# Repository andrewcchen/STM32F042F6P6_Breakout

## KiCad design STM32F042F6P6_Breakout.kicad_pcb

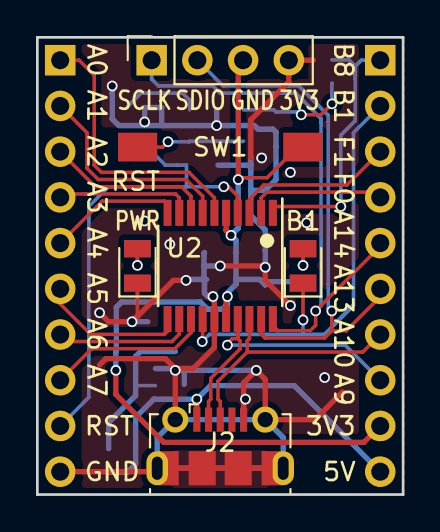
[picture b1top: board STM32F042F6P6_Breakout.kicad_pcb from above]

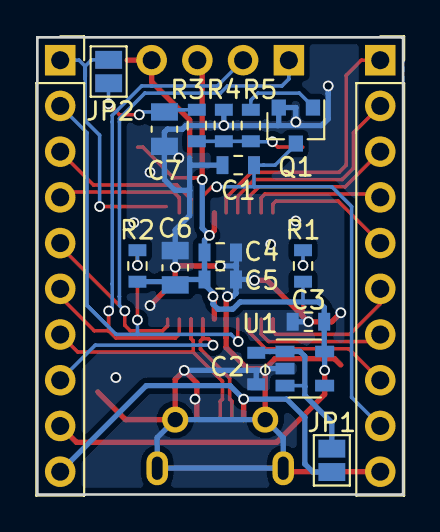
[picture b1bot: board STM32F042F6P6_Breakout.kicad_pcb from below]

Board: 2 copper layers, 20.3 x 25.4 mm, 24 parts (18 on the bottom side), 26 nets.

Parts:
C1, C4, C5: 100nF; C_0603_1608Metric
C2, C3: 1uF; C_0603_1608Metric
C6, C7: 10uF; C_0805_2012Metric
D1, D2: LED; LED_0805_2012Metric
J1, J3: Conn_01x10_Male; PinSocket_1x10_P2.54mm_Vertical
J2: USB_B_Micro; USB_Micro-B_Molex-105017-0001
J4: Conn_01x04_Male; PinSocket_1x04_P2.54mm_Vertical
JP1, JP2: SolderJumper; SolderJumper-2_P1.3mm_Open_Pad1.0x1.5mm
Q1: Q_NPN; SOT-23
R1, R2: 470; R_0603_1608Metric
R3: 330k; R_0603_1608Metric
R4, R5: 10k; R_0603_1608Metric
SW1: SW_Push; SW_SPST_FSMSM
U1: TLV70033_SOT23-5; SOT-23-5
U2: STM32F042F6Px; TSSOP-20_4.4x6.5mm_P0.65mm

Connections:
+3V3: C3.1, C4.1, C5.1, C6.1, J3.9, J4.3, R1.1, R2.1, SW1.1, U1.5, U2.5, U2.16
/BOOT0: C7.1, JP2.1, R3.1
/NRST: C1.1, J1.9, Q1.3, U2.4
/PA0: J1.1, U2.6
/PA1: J1.2, U2.7
/PA2: J1.3, U2.8
/PA3: J1.4, U2.9
/PA4: J1.5, U2.10
/PA5: J1.6, U2.11
/PA6: J1.7, U2.12
/PA7: J1.8, U2.13
/PB1: D2.1, J3.2, U2.14
/PB8: J3.1, JP2.2, U2.1
/PF0: J3.4, U2.2
/PF1: J3.3, U2.3
/RST_SW: R3.2, R4.1, R5.2, SW1.2
/VBUS: J2.1, J3.10, JP1.1
/V_IN: C2.1, JP1.2, U1.1, U1.3
GND: C1.2, C2.2, C3.2, C4.2, C5.2, C6.2, C7.2, D1.1, J1.10, J2.5, J2.6, J4.4, Q1.2, R4.2, U1.2, U2.15
unnamed: D1.2, R1.2
unnamed: D2.2, R2.2
unnamed: Q1.1, R5.1
SWCLK: J3.5, J4.1, U2.20
SWDIO: J3.6, J4.2, U2.19
USB_D+: J2.3, J3.7, U2.18
USB_D-: J2.2, J3.8, U2.17

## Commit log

2018-02-06 rev 1.0
2018-02-06 rev 1.1
